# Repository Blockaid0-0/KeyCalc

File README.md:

# KeyCalc
Little macropad meant for math

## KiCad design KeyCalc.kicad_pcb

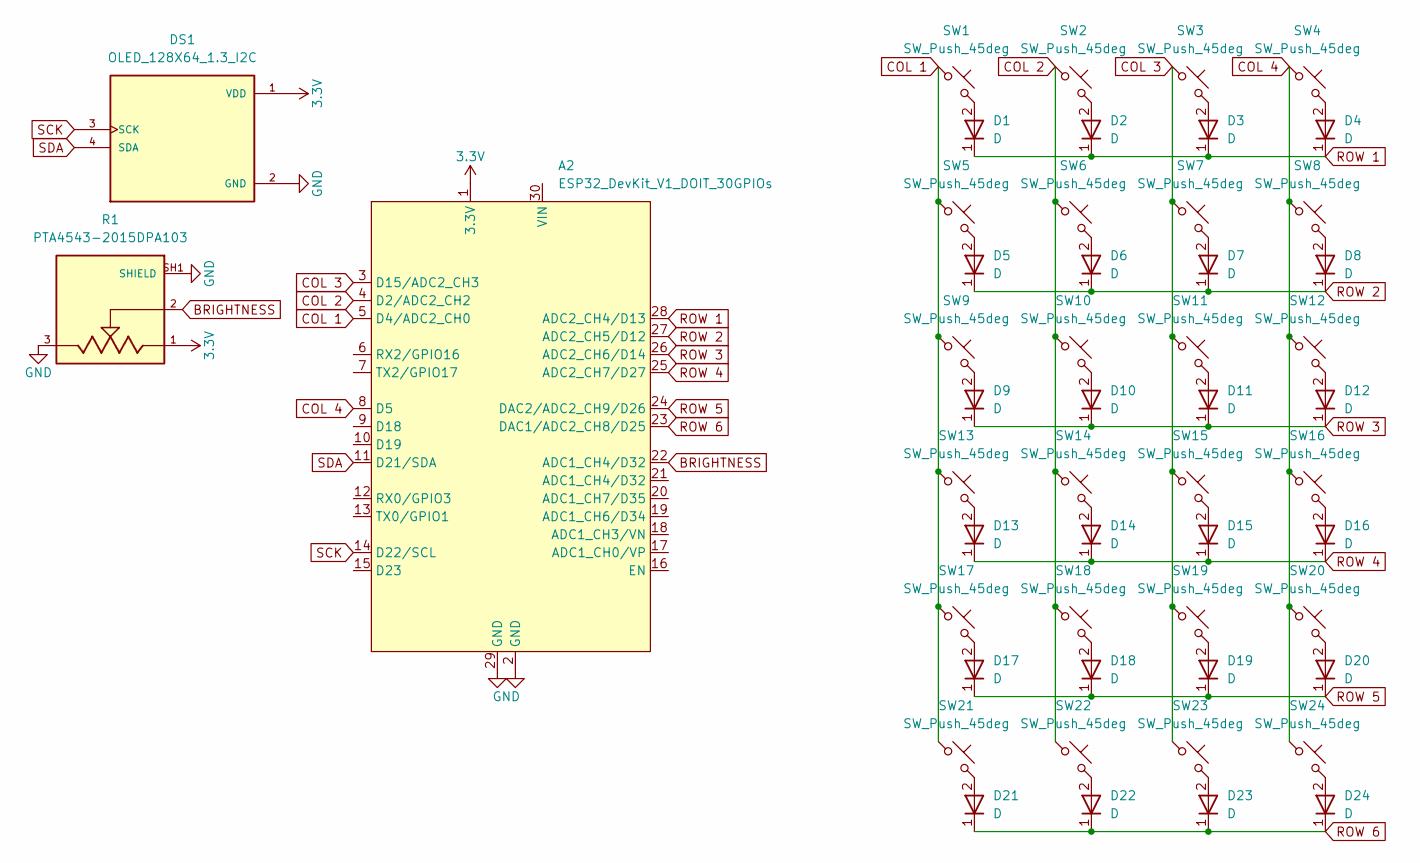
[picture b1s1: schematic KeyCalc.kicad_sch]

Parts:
A2: ESP32_DevKit_V1_DOIT_30GPIOs; DOIT_ESP32_DEVKIT_30Pins
D1, D2, D3, D4, D5, D6, D7, D8, D9, D10, D11, D12, D13, D14, D15, D16, D17, D18, D19, D20, D21, D22, D23, D24: D; D_DO-41_SOD81_P10.16mm_Horizontal
DS1: OLED_128X64_1.3_I2C; LCD_OLED_128X64_1.3_I2C; PARTREV NA
R1: PTA4543-2015DPA103; TRIM_PTA4543-2015DPA103; PARTREV 04/21
SW1, SW2, SW3, SW4, SW5, SW6, SW7, SW8, SW9, SW10, SW11, SW12, SW13, SW14, SW15, SW16, SW17, SW18, SW19, SW20, SW21, SW22, SW23, SW24: SW_Push_45deg; SW_Cherry_MX_PCB

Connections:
3.3V: A2.1 (3.3V), DS1.1 (VDD), R1.1
BRIGHTNESS: A2.22 (ADC1_CH4/D32), R1.2
COL 1: A2.5 (D4/ADC2_CH0), SW1.1, SW5.1, SW9.1, SW13.1, SW17.1, SW21.1
COL 2: A2.4 (D2/ADC2_CH2), SW2.1, SW6.1, SW10.1, SW14.1, SW18.1, SW22.1
COL 3: A2.3 (D15/ADC2_CH3), SW3.1, SW7.1, SW11.1, SW15.1, SW19.1, SW23.1
COL 4: A2.8 (D5), SW4.1, SW8.1, SW12.1, SW16.1, SW20.1, SW24.1
GND: A2.2 (GND), A2.29 (GND), DS1.2 (GND), R1.3, R1.SH1 (SHIELD), R1.SH2 (SHIELD), R1.SH3 (SHIELD), R1.SH4 (SHIELD)
unnamed: D1.2 (A), SW1.2
unnamed: D2.2 (A), SW2.2
unnamed: D3.2 (A), SW3.2
unnamed: D4.2 (A), SW4.2
unnamed: D5.2 (A), SW5.2
unnamed: D6.2 (A), SW6.2
unnamed: D7.2 (A), SW7.2
unnamed: D8.2 (A), SW8.2
unnamed: D9.2 (A), SW9.2
unnamed: D10.2 (A), SW10.2
unnamed: D11.2 (A), SW11.2
unnamed: D12.2 (A), SW12.2
unnamed: D13.2 (A), SW13.2
unnamed: D14.2 (A), SW14.2
unnamed: D15.2 (A), SW15.2
unnamed: D16.2 (A), SW16.2
unnamed: D17.2 (A), SW17.2
unnamed: D18.2 (A), SW18.2
unnamed: D19.2 (A), SW19.2
unnamed: D20.2 (A), SW20.2
unnamed: D21.2 (A), SW21.2
unnamed: D22.2 (A), SW22.2
unnamed: D23.2 (A), SW23.2
unnamed: D24.2 (A), SW24.2
ROW 1: A2.28 (ADC2_CH4/D13), D1.1 (K), D2.1 (K), D3.1 (K), D4.1 (K)
ROW 2: A2.27 (ADC2_CH5/D12), D5.1 (K), D6.1 (K), D7.1 (K), D8.1 (K)
ROW 3: A2.26 (ADC2_CH6/D14), D9.1 (K), D10.1 (K), D11.1 (K), D12.1 (K)
ROW 4: A2.25 (ADC2_CH7/D27), D13.1 (K), D14.1 (K), D15.1 (K), D16.1 (K)
ROW 5: A2.24 (DAC2/ADC2_CH9/D26), D17.1 (K), D18.1 (K), D19.1 (K), D20.1 (K)
ROW 6: A2.23 (DAC1/ADC2_CH8/D25), D21.1 (K), D22.1 (K), D23.1 (K), D24.1 (K)
SCK: A2.14 (D22/SCL), DS1.3 (SCK)
SDA: A2.11 (D21/SDA), DS1.4 (SDA)

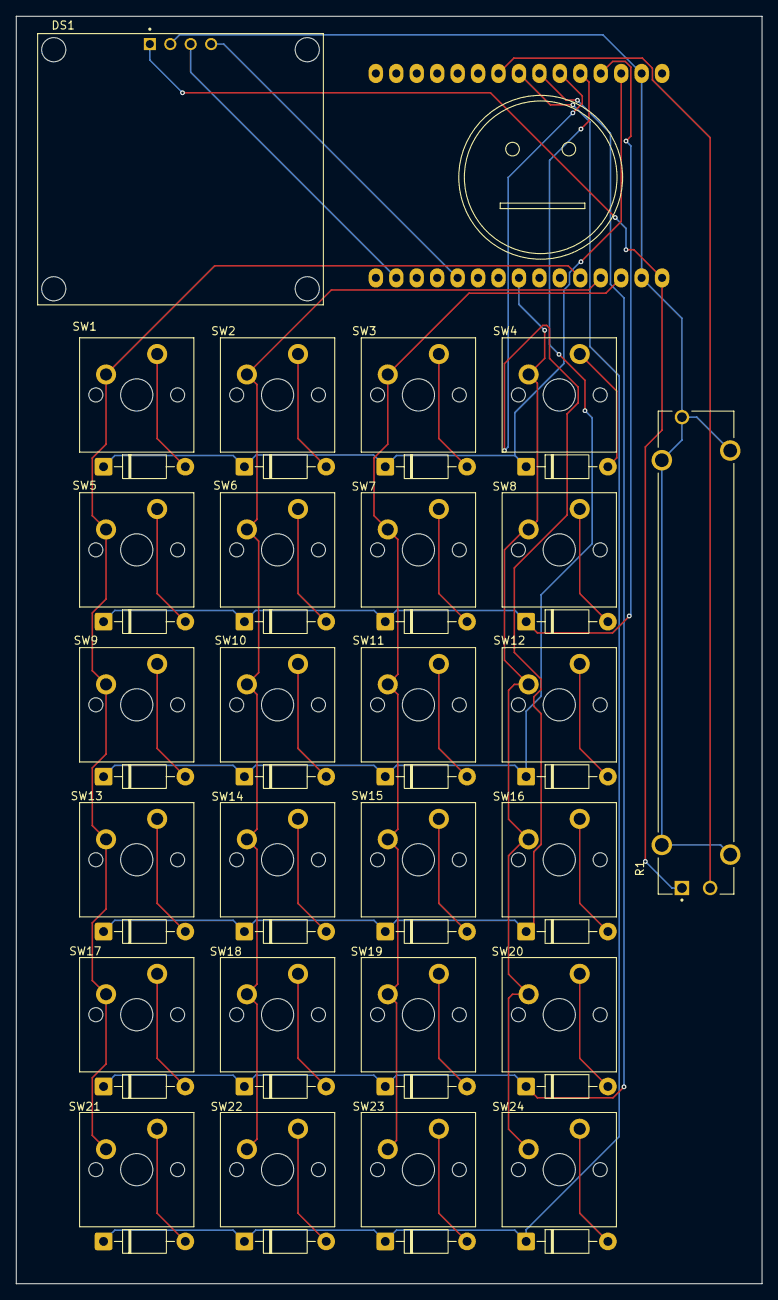
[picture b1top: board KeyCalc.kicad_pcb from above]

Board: 2 copper layers, 92.7 x 157.5 mm, 51 parts (1 on the bottom side), 39 nets.
